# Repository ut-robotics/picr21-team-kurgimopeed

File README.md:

# picr21-team-kurgimopeed

## Usage

`sudo uvicorn app:app --port 5000` - start admin web view (in backend dir). port is configured in `/etc/nginx/nginx.conf`. root is required for led drivers and realsense (nice arch plugdev)

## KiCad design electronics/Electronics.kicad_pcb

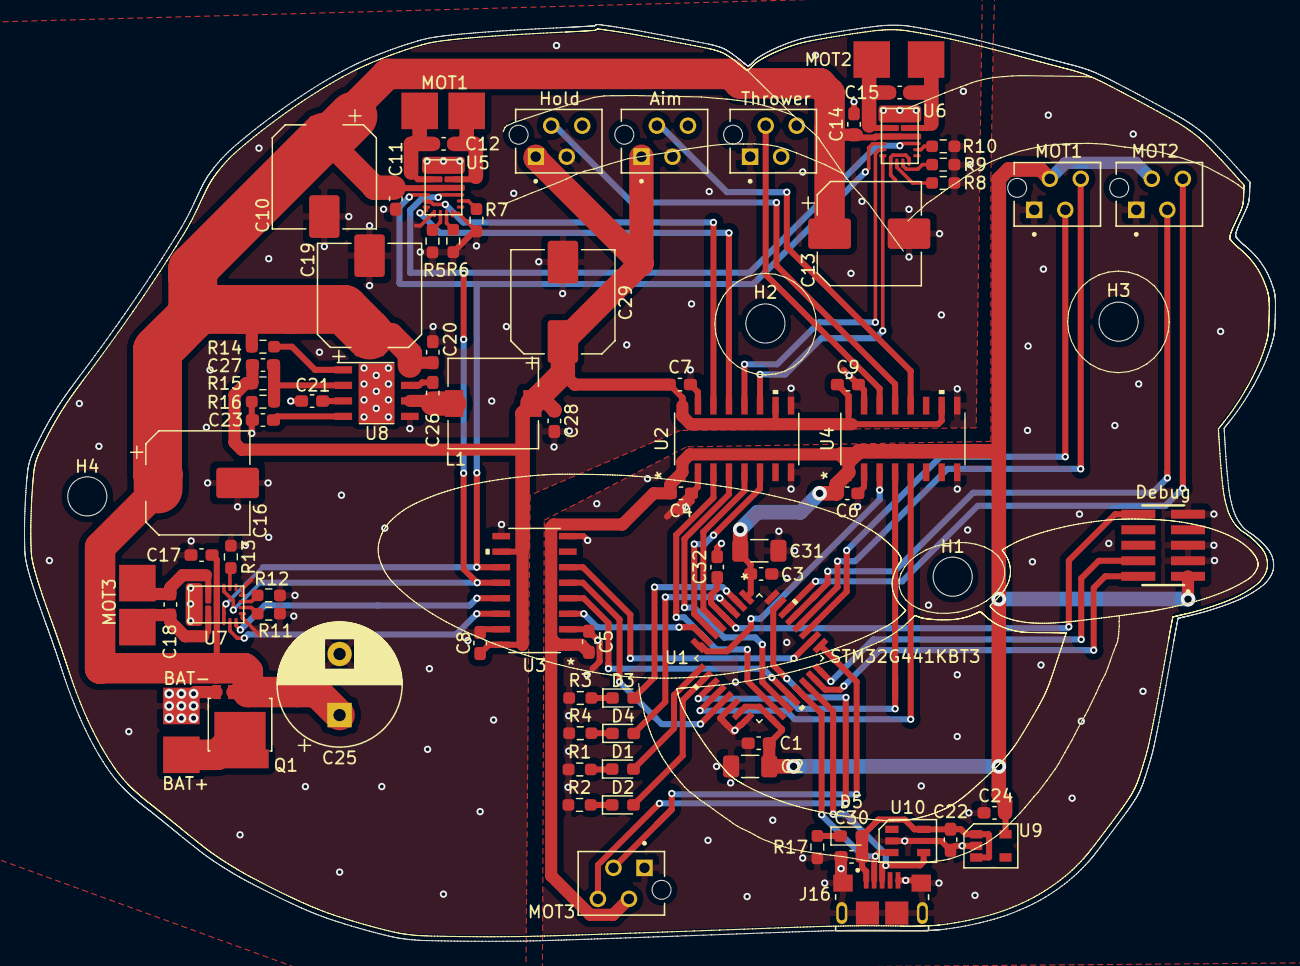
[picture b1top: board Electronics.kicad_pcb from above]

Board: 4 copper layers, 102.4 x 75.0 mm, 86 parts (0 on the bottom side), 70 nets.

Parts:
Aim: 215079-4; TE_215079-4
BAT+: 3mm_pad
BAT-: 3mm_pad
C1, C3, C4, C5, C6, C7, C8, C9, C11, C14, C17, C20, C26, C28, C30, C32: 0.1uF; C_0603_1608Metric_Pad1.08x0.95mm_HandSolder
C2, C31: 4.7uF; C_1206_3216Metric_Pad1.33x1.80mm_HandSolder
C10, C13, C16, C19, C29: 100uF; CP_Elec_8x10
C12, C15, C18: 100nF; C_0603_1608Metric_Pad1.08x0.95mm_HandSolder
C21, C22, C24: 1uF; C_0603_1608Metric_Pad1.08x0.95mm_HandSolder
C23: 3.3nF; C_0603_1608Metric_Pad1.08x0.95mm_HandSolder
C25: 470uF; CP_Radial_D10.0mm_P5.00mm
C27: 10pF; C_0603_1608Metric_Pad1.08x0.95mm_HandSolder
D1, D2: RED_LED; LED_0603_1608Metric_Pad1.05x0.95mm_HandSolder
D3, D4: GREEN_LED; LED_0603_1608Metric_Pad1.05x0.95mm_HandSolder
D5: RED_LED; D_0603_1608Metric_Pad1.05x0.95mm_HandSolder
Debug: FTSH-105-XX-X-DV; SAMTEC_FTSH-105-XX-X-DV
H1, H2, H3, H4: MountingHole; MountingHole_3.2mm_M3
Hold: 215079-4; TE_215079-4
J2, J4, J5: 3mm_pad
J16: 10118193-0001LF; FCI_10118193-0001LF
L1: 4.7uH; L_7.3x7.3_H4.5
MOT1, MOT2, MOT3: 3mm_pad
MOT1#2, MOT2#2, MOT3#2: 215079-4; TE_215079-4
Q1: BUK6Y10-30P; LFPAK56
R1, R2, R3, R4, R17: 3.3k; R_0603_1608Metric_Pad0.98x0.95mm_HandSolder
R5, R6, R8, R9, R11, R12: 100k; R_0603_1608Metric_Pad0.98x0.95mm_HandSolder
R7, R10, R13: 2.7k; R_0603_1608Metric_Pad0.98x0.95mm_HandSolder
R14: 10k; R_0603_1608Metric_Pad0.98x0.95mm_HandSolder
R15: 130k; R_0603_1608Metric_Pad0.98x0.95mm_HandSolder
R16: 22k; R_0603_1608Metric_Pad0.98x0.95mm_HandSolder
Thrower: 215079-4; TE_215079-4
U1: STM32G441KBT3
U2, U3, U4: MAX14930DASE+; MAX14930DASE&plus_
U5, U6, U7: DRV8243; VQFN-HR-14
U8: TPS54227DDAR
U9: NCP164
U10: CM1223-02SO

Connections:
+3V3: C1.1, C2.1, C3.1, C4.2, C5.2, C6.2, C24.1, C31.2, Debug.01, MOT1#2.2, MOT2#2.2, MOT3#2.2, U1.1, U1.15, U1.17, U2.1, U3.1, U4.1, U9.5
+5VD: Aim.1, C7.1, C8.1, C9.1, C27.2, C28.2, C29.1, Hold.1, L1.2, R15.1, U2.10, U2.16, U3.10, U3.16, U4.10, U4.16
+5VL: C22.1, C30.2, D5.2, J16.1, U9.1, U9.3, U10.5
/Aim-serv_PWM: Aim.2, U4.12
/Driver/MOT1en_1: U2.14, U5.9
/Driver/MOT1en_2: U2.13, U5.10
/Driver/MOT2en_1: U2.12, U6.9
/Driver/MOT2en_2: U2.11, U6.10
/Driver/MOT3en_1: U3.14, U7.9
/Driver/MOT3en_2: U3.13, U7.10
/Driver/MOT_off: U3.11, U5.8, U6.8, U7.8
/Driver/MOT_sleep: U3.12, U5.3, U6.3, U7.3
/Hold-serv_PWM: Hold.2, U4.13
/MCU-Aim-serv_PWM: U1.12, U4.5
/MCU-Hold-serv_PWM: U1.11, U4.4
/MCU-MOT1en_1: U1.18, U2.3
/MCU-MOT1en_2: U1.19, U2.4
/MCU-MOT2en_1: U1.5, U2.5
/MCU-MOT2en_2: U1.6, U2.6
/MCU-MOT3en_1: U1.7, U3.3
/MCU-MOT3en_2: U1.20, U3.4
/MCU-TRW_PWM: U1.8, U4.3
/MCU-USB_DM: J16.2, U1.21, U10.3
/MCU-USB_DP: J16.3, U1.22, U10.4
/MCU-debug-LED_G1: D3.2, U1.2
/MCU-debug-LED_G2: D4.2, U1.3
/MCU-debug-LED_R1: D1.2, U1.9
/MCU-debug-LED_R2: D2.2, U1.10
/MCU-mot1-enc_1: MOT1#2.3, U1.27
/MCU-mot1-enc_2: MOT1#2.4, U1.28
/MCU-mot2-enc_1: MOT2#2.3, U1.29
/MCU-mot2-enc_2: MOT2#2.4, U1.30
/MCU-mot3-enc_1: MOT3#2.3, U1.25
/MCU-mot3-enc_2: MOT3#2.4, U1.31
/MCU-mot_off: U1.26, U3.6
/MCU-mot_sleep: U1.13, U3.5
/MCU_NRST: C32.1, Debug.10, U1.4
/MCU_SWCLK: Debug.04, U1.24
/MCU_SWDIO: Debug.02, U1.23
/TRW_PWM: Thrower.2, U4.14
Earth: Aim.3, BAT-.1, C7.2, C8.2, C9.2, C10.2, C11.1, C13.2, C14.1, C16.2, C17.1, C19.2, C20.1, C21.1, C23.1, C25.2, C28.1, C29.2, Hold.3, Q1.4, R5.1, R6.1, R7.1, R8.1, R9.1, R10.1, R11.1, R12.1, R13.1, R16.2, Thrower.1, U2.9, U2.15, U3.9, U3.15, U4.9, U4.15, U5.6, U5.11, U5.14, U6.6, U6.11, U6.14, U7.6, U7.11, U7.14, U8.5, U8.9
GND: C1.2, C2.2, C3.2, C4.1, C5.1, C6.1, C22.2, C24.2, C30.1, C31.1, C32.2, Debug.03, Debug.05, Debug.09, J16.5, J16.S1, J16.S2, J16.S3, J16.S4, J16.S5, J16.S6, MOT1#2.1, MOT2#2.1, MOT3#2.1, R1.1, R2.1, R3.1, R4.1, R17.1, U1.14, U1.16, U1.32, U2.2, U2.8, U3.2, U3.8, U4.2, U4.8, U9.2, U10.2
unnamed: C12.1, MOT1.1, U5.7
unnamed: C12.2, J2.1, U5.5
unnamed: C15.1, MOT2.1, U6.7
unnamed: C15.2, J4.1, U6.5
unnamed: C18.1, J5.1, U7.7
unnamed: C18.2, MOT3.1, U7.5
unnamed: C21.2, U8.3
unnamed: C23.2, U8.4
unnamed: C26.1, U8.7
unnamed: C26.2, L1.1, U8.6
unnamed: C27.1, R15.2, R16.1, U8.2
unnamed: D1.1, R1.2
unnamed: D2.1, R2.2
unnamed: D3.1, R3.2
unnamed: D4.1, R4.2
unnamed: D5.1, R17.2
unnamed: BAT+.1, Q1.5
unnamed: R5.2, U5.12
unnamed: R6.2, U5.13
unnamed: R7.2, U5.2
unnamed: R8.2, U6.12
unnamed: R9.2, U6.13
unnamed: R10.2, U6.2
unnamed: R11.2, U7.12
unnamed: R12.2, U7.13
unnamed: R13.2, U7.2
unnamed: R14.2, U8.1
Vdrive: C10.1, C11.2, C13.1, C14.2, C16.1, C17.2, C19.1, C20.2, C25.1, Q1.1, Q1.2, Q1.3, R14.1, U5.4, U6.4, U7.4, U8.8

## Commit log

2021-09-20 nuc led library
2021-09-20 Add wip flask backend, realsense camera feed
2021-09-27 Moved electronics from bitbucket to here
2021-09-27 initial motor driver
2021-09-27 work on rs
2021-09-28 Updated and removed unnecessary resistors, removed cache
2021-09-30 support multiple feed service, add depth
2021-10-04 working robot remote control, major updates
2021-10-07 add functioning arrow key control, add nuc led status
2021-10-09 Reorganised schematics, added regulators
2021-10-09 Added battery pads, documented voltage regulators
2021-10-11 work on things :)
2021-10-14 work on image processing, threshold balls, black line, white line
2021-10-18 Add cpu conf
2021-10-18 fix #8
2021-10-18 fix #9
2021-10-18 fix BIG bug crash on file read/read, 2000post/s brrrrrrrr
2021-10-18 Added isolators, updated CPU pins
2021-10-18 add nuc speaker support without speaker
2021-10-19 Added servo pins
2021-10-21 Added connectors, started relabeling pins
2021-10-21 Made seperate music class
2021-10-21 music lib
2021-10-21 Another restructure, added CPU pins, updated V regulators
2021-10-21 LED fix
2021-10-21 Updated titles
2021-10-21 fixed music
2021-10-21 add risen, work on court webview, ar detection magic
2021-10-23 Made things prettier, lowered logic 3v3 LDO back to 300mA
2021-10-23 Removed unnecessary files
2021-10-23 Updated symbols
2021-10-23 new piece
2021-10-23 Added reverse polarity protection
2021-10-23 Added debug LEDs
2021-10-23 Removed redundant comments
2021-10-24 Various fixes, added ESD protection
2021-10-24 Remapped MCU
2021-10-24 Updated rev numbers
2021-10-24 Added background colors to symbols
2021-10-25 Replaced 5V regulator
2021-10-25 Removed cache file
2021-10-25 MOSFET fix
2021-10-25 new music, ball detection and localication (not tested)
2021-10-26 Updated gitignore, switched out regulator
2021-10-28 ball detection, cord calculation
2021-10-28 big work
2021-10-31 Attached footprints to components
2021-11-01 Spurdo commit
2021-11-01 Added models to footprints
2021-11-01 Ragn-sells
2021-11-01 Relocated libs, renamed MCU
2021-11-01 Relocated 3d models
2021-11-01 Re-added footprints, removed excess model
2021-11-01 Figured out how to automatically change date and revision
2021-11-01 Did the same to pcb
2021-11-02 Relocated items
2021-11-02 good update
    please approve, sir
2021-11-02 Moved usb
2021-11-02 Sorting componenents on pcb
2021-11-06 Fixed motor connectors, added vbat to 5v
2021-11-06 Great success
2021-11-07 Added MCU to main pcb
2021-11-07 Benis :DDDDDDDDDDDDDDDDDDDDD
2021-11-07 Removed 2 vias, added thermal vias
2021-11-07 Allahu akbar
2021-11-07 Why are we still here? Just to suffer?
2021-11-08 BIG update (ball 3d location resolved 88))))
2021-11-09 Updated item locations
2021-11-11 work on game logic
2021-11-11 Started drawing new traces
2021-11-15 update configs
2021-11-16 Motor connections done
2021-11-16 MCU connections done v2
2021-11-16 Filled empty areas
2021-11-16 Rev2 Done?
2021-11-16 Added 3d model for inductor
2021-11-16 Updated rev and date
2021-11-16 Typo fix
2021-11-16 Fixus trace
2021-11-18 Spurdo v2.1 update
2021-11-18 Silk fixes
2021-11-20 Added vias
2021-11-20 Updated dates and rev nr
2021-11-21 Added BOM, gerber and drillhole files
2021-11-22 Added schematic PDF
2021-11-22 Set up firmware development environment
2021-11-25 work on thrower lut
2021-11-29 Bad apple
2021-12-02 good enough for competition
2021-12-06 detection optimizatsions, almost working border detection
2021-12-06 new thresholds
2021-12-06 added area of interest for borderdetection
2021-12-09 detection optimizations
2021-12-16 refactor code; add referee server
2021-12-16 Added USB support
2021-12-16 treat stop as blocking importat data to send to motors
2021-12-17 Actually added USB support
2021-12-18 Drivinglogic cleanup
2021-12-31 CRC now works lol
2022-01-01 CRC fixed, created an interfacing program
2022-01-03 fixed remote control delay and constant stopping
2022-01-05 PWM works in debug, not in run
2022-01-11 Added direction control
2022-01-11 Updated speed control
2022-01-13 Keskkonnateenused
2022-01-13 Object files bye bye
2022-01-13 Local settings removal
2022-01-13 Added PID control
2022-01-13 Added comments
2022-01-13 De-duplicated nSleep pulsing
2022-01-19 Change file mode, added ball interrupt
2022-01-24 tested all motors, added hold and angle servo, new music map, new mainboard comm
2022-01-24 undo anti mainboard spam
2022-01-24 new logic for new thrower
2022-01-24 cant remeber what i have done
2022-01-24 no glue
2022-01-25 new thrower data
2022-01-25 PID works, firmware done
2022-01-26 Paha õun
2022-01-26 allnighter xd
2022-01-26 only hope
2022-01-26 competition ready?, backup
2022-01-26 Complete failure, thank you, come again

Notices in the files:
parts and their libraries:
Copyright 2021 Accelerated Designs. All rights reserved.
